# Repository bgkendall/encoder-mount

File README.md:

# Encoder Mount PCB

This is a simple PCB for mounting [EC11]-type rotary encoders. It is intended for use in keyboard
projects and provides an alternative mounting option for securing an encoder as well as easier
wiring into a keyboard matrix. This repository contains the [KiCad] PCB design files and [Gerber
format] files for PCB production. Zipped Gerber packages are included in the release assets.

## Sizes

The PCB comes in two sizes:

 * **0.1″ spacing** – 23×16mm — the break-out pins are 8×0.1″ (20.32mm) apart and should therefore
   be compatible with standard breadboards and prototype PCBs.
 * **tight** — 20.7×15.6mm — this is a smaller board for fitting into tighter spaces.

Both sizes have the same functionality.

## Mounting

The PCB provides four M2 mounting holes to provide a sturdy base for the encoder when it is bolted
to the keyboard’s plate or base. The PCB can also be used with Kevin Eckert’s [EC11 to MX
Switchplate Adapter][ec112mx].

When using an encoder that has a base with a central pillar and four legs on the corners (as shown
below), the outer legs can be clipped and/or sanded. Both boards provide space for the pillar, which
allows for a more compact installation.

Genuine ALPS EC11 encoders have even squatter bases, but, in addition to typically being more
expensive, do not appear to be available with threaded collars. This may mean they are impractical
in some situations, although the M2 mounting holes on these PCBs may reopen some possibilities.

## Wiring

### Encoder

The PCB breaks out the following pins as labelled on the PCB:

 * `A` — encoder A pin
 * `G` — the common or ground pin
 * `B` — encoder B pin

### Switch

To access the push switch pins the following are used:

 * `C/1`
 * `G/2`

However there are a couple of extra features to improve handling of the switch when used in a
keyboard.

#### Standard Keyboard Matrix

If used in a standard [keyboard matrix], a 1N4841 [SOD-123] SMD diode can be soldered in position
`D1`, with the direction depending on whether the matrix is Column-to-Row or Row-to-Column. The
labels `C2R|` and `|R2C` indicate the correct orientation for each of these matrix directions.

If D1 is populated, then the switch is connected as follows:

 * `R` — the switch’s row
 * `C/1` — the switch’s column

#### Direct Pin Matrix

If a [direct pin matrix] is used, where each switch is wired between ground and a separate I/O
pin, then the connection to ground can optionally be made by soldering across jumper `JP1`.

In this case, the switch is wired as follows:

 * `C/1` — to the switch’s I/O pin
 * `G/2` — can be left unconnected, wired to another switch, or can be connected to ground *instead
   of* `G`

[EC11]: https://tech.alpsalpine.com/e/products/detail/EC11E15204A3/
[KiCad]: https://www.kicad.org
[Gerber format]: https://en.wikipedia.org/wiki/Gerber_format
[ec112mx]: https://www.thingiverse.com/thing:3770166
[keyboard matrix]: https://www.pcbheaven.com/wikipages/How_Key_Matrices_Works/
[SOD-123]: https://en.wikipedia.org/wiki/Small_Outline_Diode
[direct pin matrix]: https://docs.qmk.fm/#/porting_your_keyboard_to_qmk?id=direct-pin-matrix

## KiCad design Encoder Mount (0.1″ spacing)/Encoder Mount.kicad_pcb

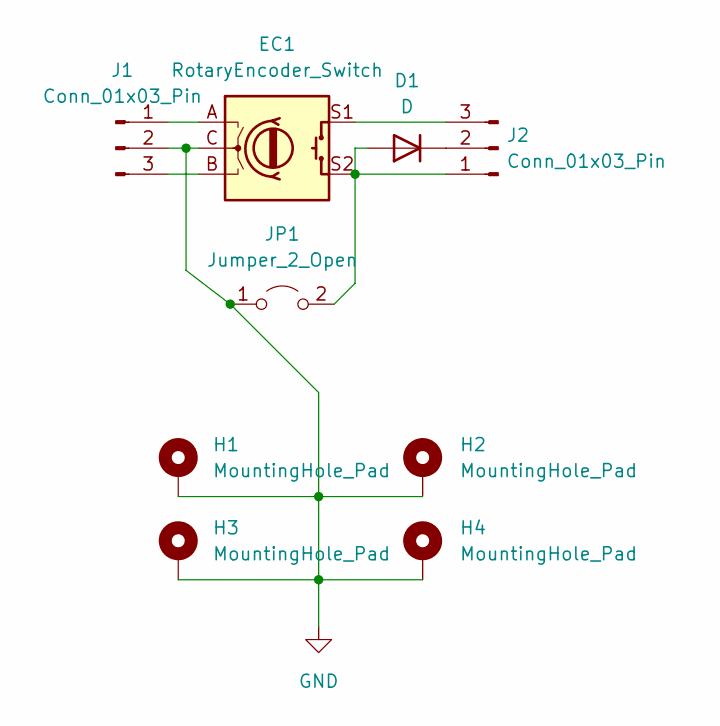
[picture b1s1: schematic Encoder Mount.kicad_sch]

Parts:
D1: D; D_SOD-123
EC1: RotaryEncoder_Switch; RotaryEncoder_Alps_EC11E-Switch_Vertical_H20mm_CircularMoun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
H1, H2, H3, H4: MountingHole_Pad
J1, J2: Conn_01x03_Pin; PinHeader_1x03_P2.54mm_Vertical
JP1: Jumper_2_Open; SolderJumper-2_P1.3mm_Open_TrianglePad1.0x1.5mm

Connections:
GND: EC1.C, H1.1, H2.1, H3.1, H4.1, J1.2, JP1.1 (A)
unnamed: D1.2 (A), EC1.S2, J2.1, JP1.2 (B)
unnamed: D1.1 (K), J2.2
unnamed: EC1.A, J1.1
unnamed: EC1.B, J1.3
unnamed: EC1.S1, J2.3

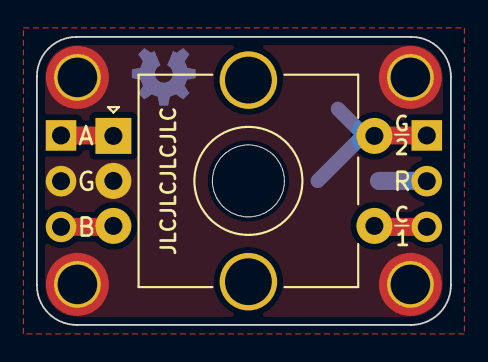
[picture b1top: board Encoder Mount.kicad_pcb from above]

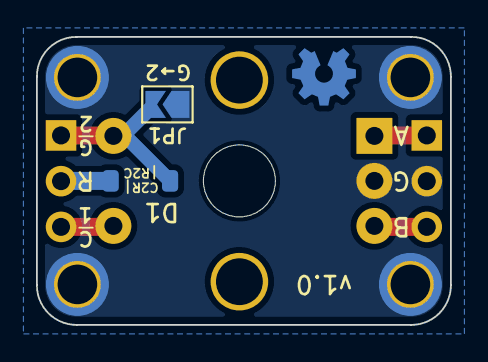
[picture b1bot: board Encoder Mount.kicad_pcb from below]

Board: 2 copper layers, 23.0 x 16.0 mm, 9 parts (2 on the bottom side), 6 nets.

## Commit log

2023-08-31 Initial check-in of Encoder Mount PCB files
2023-09-02 Add version number and tweak alignment
2023-09-02 Add board images and update README
2023-09-02 Update ground clearance and edge corner radius
2023-09-02 Add note about central hole
2023-09-02 Added note on genuine ALPS encoders
2023-09-18 Update board top images to show correct proportions between the two sizes
2023-09-18 Add mention of EC11 to MX adaptor to README
2023-09-18 Add Gerber plots for Encoder Mount (tight)
2023-09-18 Add Gerber plots for Encoder Mount (0.1″ spacing)
2023-09-18 Add JLC order number locator
    See [“ How to remove order number from your PCB?”](https://jlcpcb.com/help/article/50-How-to-remove-order-number-from-your-PCB)
2023-09-18 Ignore Gerber ZIPs
    These will be attached to releases instead.
2024-03-20 Fix typo
